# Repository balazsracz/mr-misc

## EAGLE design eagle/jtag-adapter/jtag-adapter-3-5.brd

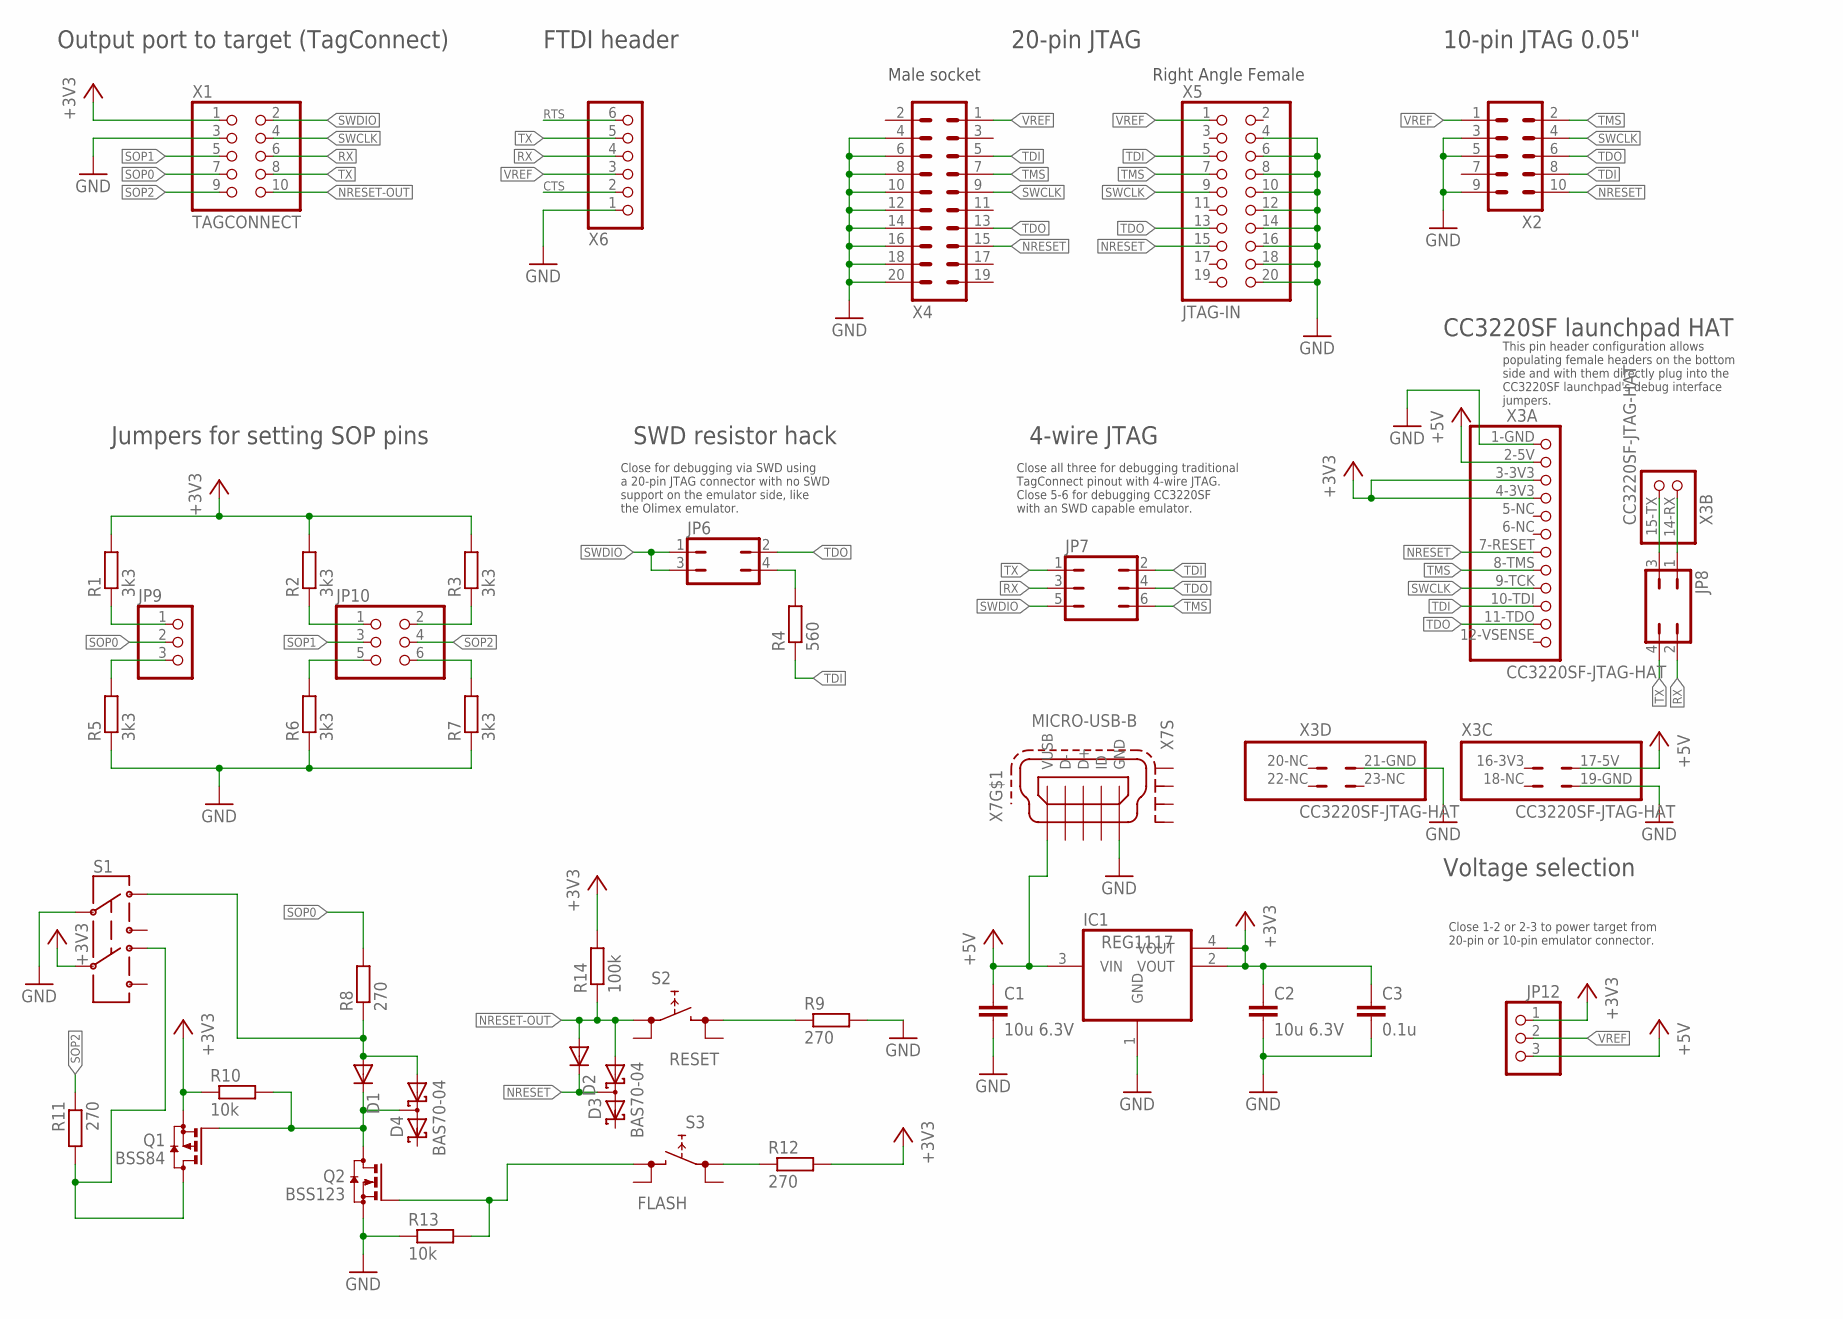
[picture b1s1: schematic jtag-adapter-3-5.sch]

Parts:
C1, C2: 10u 6.3V; C0603K
C3: 0.1u; C0603K
D1, D2: DIODE-MINIMELF; MINIMELF
D3, D4: BAS70-04; SOT23
IC1: REG1117; SOT223
JP6, JP8: JP2Q
JP7: JP3Q
JP9, JP12: PINHD-1X3; 1X03
JP10: PINHD-2X3; 2X03
Q1: BSS84; SOT23
Q2: BSS123; SOT23
R1, R2, R3, R5, R6, R7: 3k3; R0805
R4: 560; R0805
R8, R9, R11, R12: 270; R0805
R10, R13: 10k; R0805
R14: 100k; R0805
S1: SWITCH-DPDTJS202011CQN; DPDT-2.5X3.2MM
S2: RESET; TACTSW-6X6
S3: FLASH; TACTSW-6X6
X1: TAGCONNECT; CON10M
X2: MA05-2_0.05X0.05; MA05-2_0.05_X_0.05
X3: CC3220SF-JTAG-HAT; JTAG-LAUNCHPAD-3220SF
X4: MA10-2S; MA10-2-SHROUDED
X5: JTAG-IN; 2X10
X6: PINHD-1X6; 1X06
X7: MICRO-USB-B; MICRO-B-PAC

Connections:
+3V3: C2.1, C3.1, IC1.2 (VOUT), IC1.4 (VOUT), JP12.1, Q1.2 (S), R1.2, R2.2, R3.2, R10.1, R12.2, R14.2, S1.5 (2C), X1.1, X3.3-3V3 (3), X3.4-3V3 (4)
+5V: C1.1, IC1.3 (VIN), JP12.3, X3.2-5V (2), X3.17-5V (2), X7.1 (VUSB)
CTS: X6.2
FL-SOP2-PU: Q1.3 (D), R11.2, S1.4 (2A)
GND: C1.2, C2.2, C3.2, IC1.1 (GND), Q2.2 (S), R5.1, R6.1, R7.1, R9.2, R13.1, S1.2 (1C), X1.3, X2.3, X2.5, X2.9, X3.1-GND (1), X3.19-GND (4), X3.21-GND (2), X4.4, X4.6, X4.8, X4.10, X4.12, X4.14, X4.16, X4.18, X4.20, X5.4, X5.6, X5.8, X5.10, X5.12, X5.14, X5.16, X5.18, X5.20, X6.1, X7.5 (GND)
unnamed: R9.1, S2.3 (2.1)
unnamed: JP6.4, R4.2
unnamed: D1.C, D4.3 (C1A2), Q1.1 (G), Q2.3 (D), R10.2
unnamed: R12.1, S3.1 (1.1)
unnamed: Q2.1 (G), R13.2, S3.3 (2.1)
unnamed: JP8.1, X3.14-RX (1)
unnamed: JP8.3, X3.15-TX (2)
unnamed: D1.A, D4.1 (A1), R8.1, S1.1 (1A)
NRESET: D2.C, D3.3 (C1A2), X2.10, X3.7-RESET (7), X4.15, X5.15
NRESET-OUT: D2.A, D3.1 (A1), R14.1, S2.1 (1.1), X1.10
RTS: X6.6
RX: JP7.3, JP8.2, X1.6, X6.4
SOP0: JP9.2, R8.2, X1.7
SOP0H: JP9.1, R1.1
SOP0L: JP9.3, R5.2
SOP1: JP10.3, X1.5
SOP1H: JP10.1, R2.1
SOP1L: JP10.5, R6.2
SOP2: JP10.4, R11.1, X1.9
SOP2H: JP10.2, R3.1
SOP2L: JP10.6, R7.2
SWCLK: X1.4, X2.4, X3.9-TCK (9), X4.9, X5.9
SWDIO: JP6.1, JP6.3, JP7.5, X1.2
TDI: JP7.2, R4.1, X2.8, X3.10-TDI (10), X4.5, X5.5
TDO: JP6.2, JP7.4, X2.6, X3.11-TDO (11), X4.13, X5.13
TMS: JP7.6, X2.2, X3.8-TMS (8), X4.7, X5.7
TX: JP7.1, JP8.4, X1.8, X6.5
VREF: JP12.2, X2.1, X4.1, X5.1, X6.3

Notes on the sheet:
Output port to target (TagConnect)
Jumpers for setting SOP pins
4-wire JTAG
SWD resistor hack
FTDI header
20-pin JTAG
10-pin JTAG 0.05"
Right Angle Female
Male socket
Voltage selection
CC3220SF launchpad HAT
This pin header configuration allows populating female headers on the bottom side and with them directly plug into the CC3220SF launchpad's debug interface jumpers.
Close for debugging via SWD using a 20-pin JTAG connector with no SWD support on the emulator side, like the Olimex emulator.
Close all three for debugging traditional TagConnect pinout with 4-wire JTAG. Close 5-6 for debugging CC3220SF with an SWD capable emulator.
Close 1-2 or 2-3 to power target from 20-pin or 10-pin emulator connector.

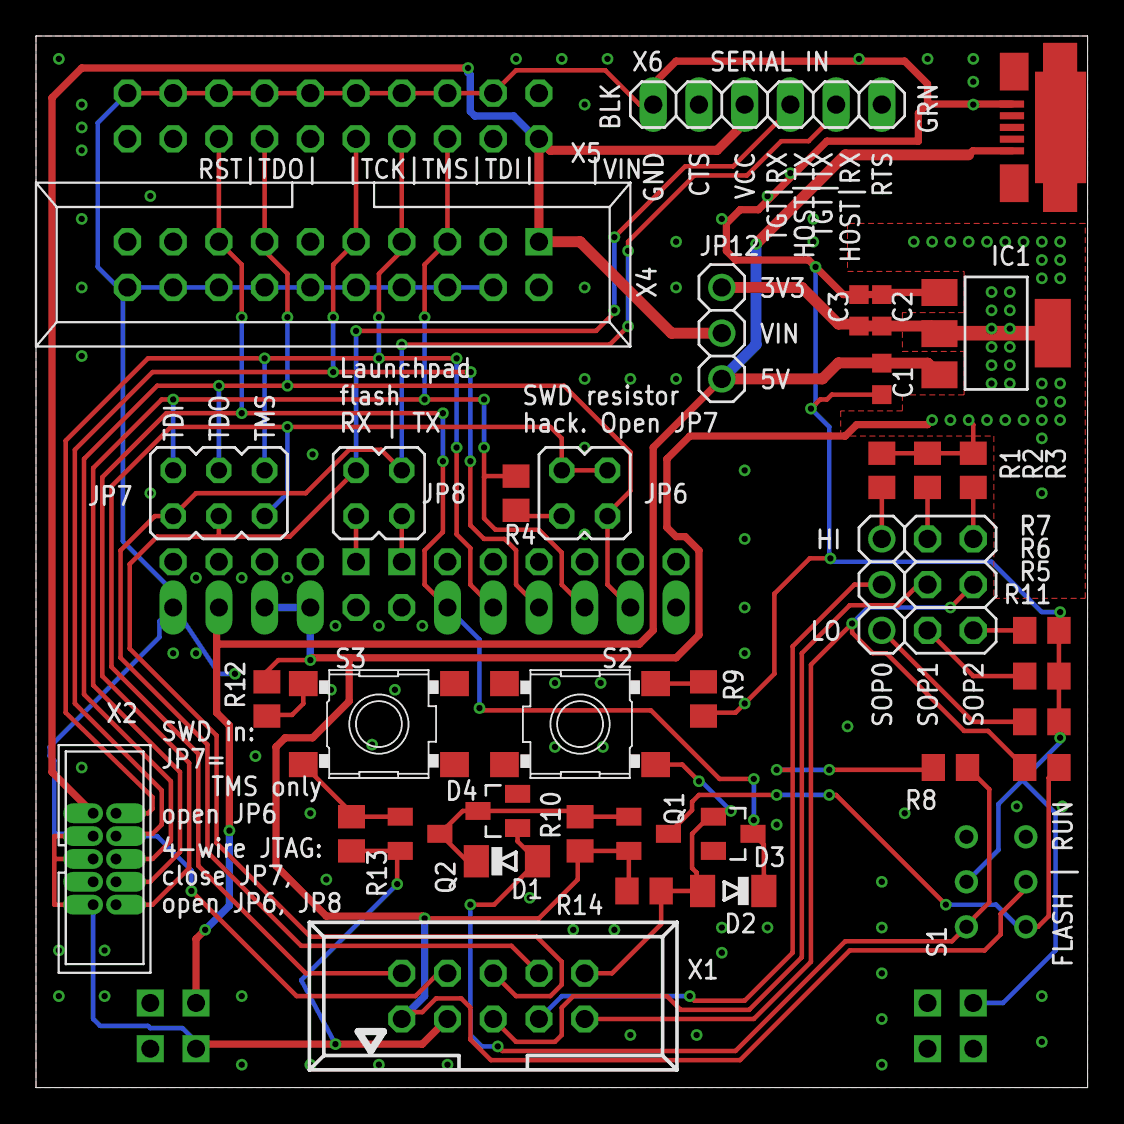
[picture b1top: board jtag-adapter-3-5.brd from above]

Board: 2 copper layers, 58.4 x 58.4 mm, 40 parts (1 on the bottom side), 31 nets.

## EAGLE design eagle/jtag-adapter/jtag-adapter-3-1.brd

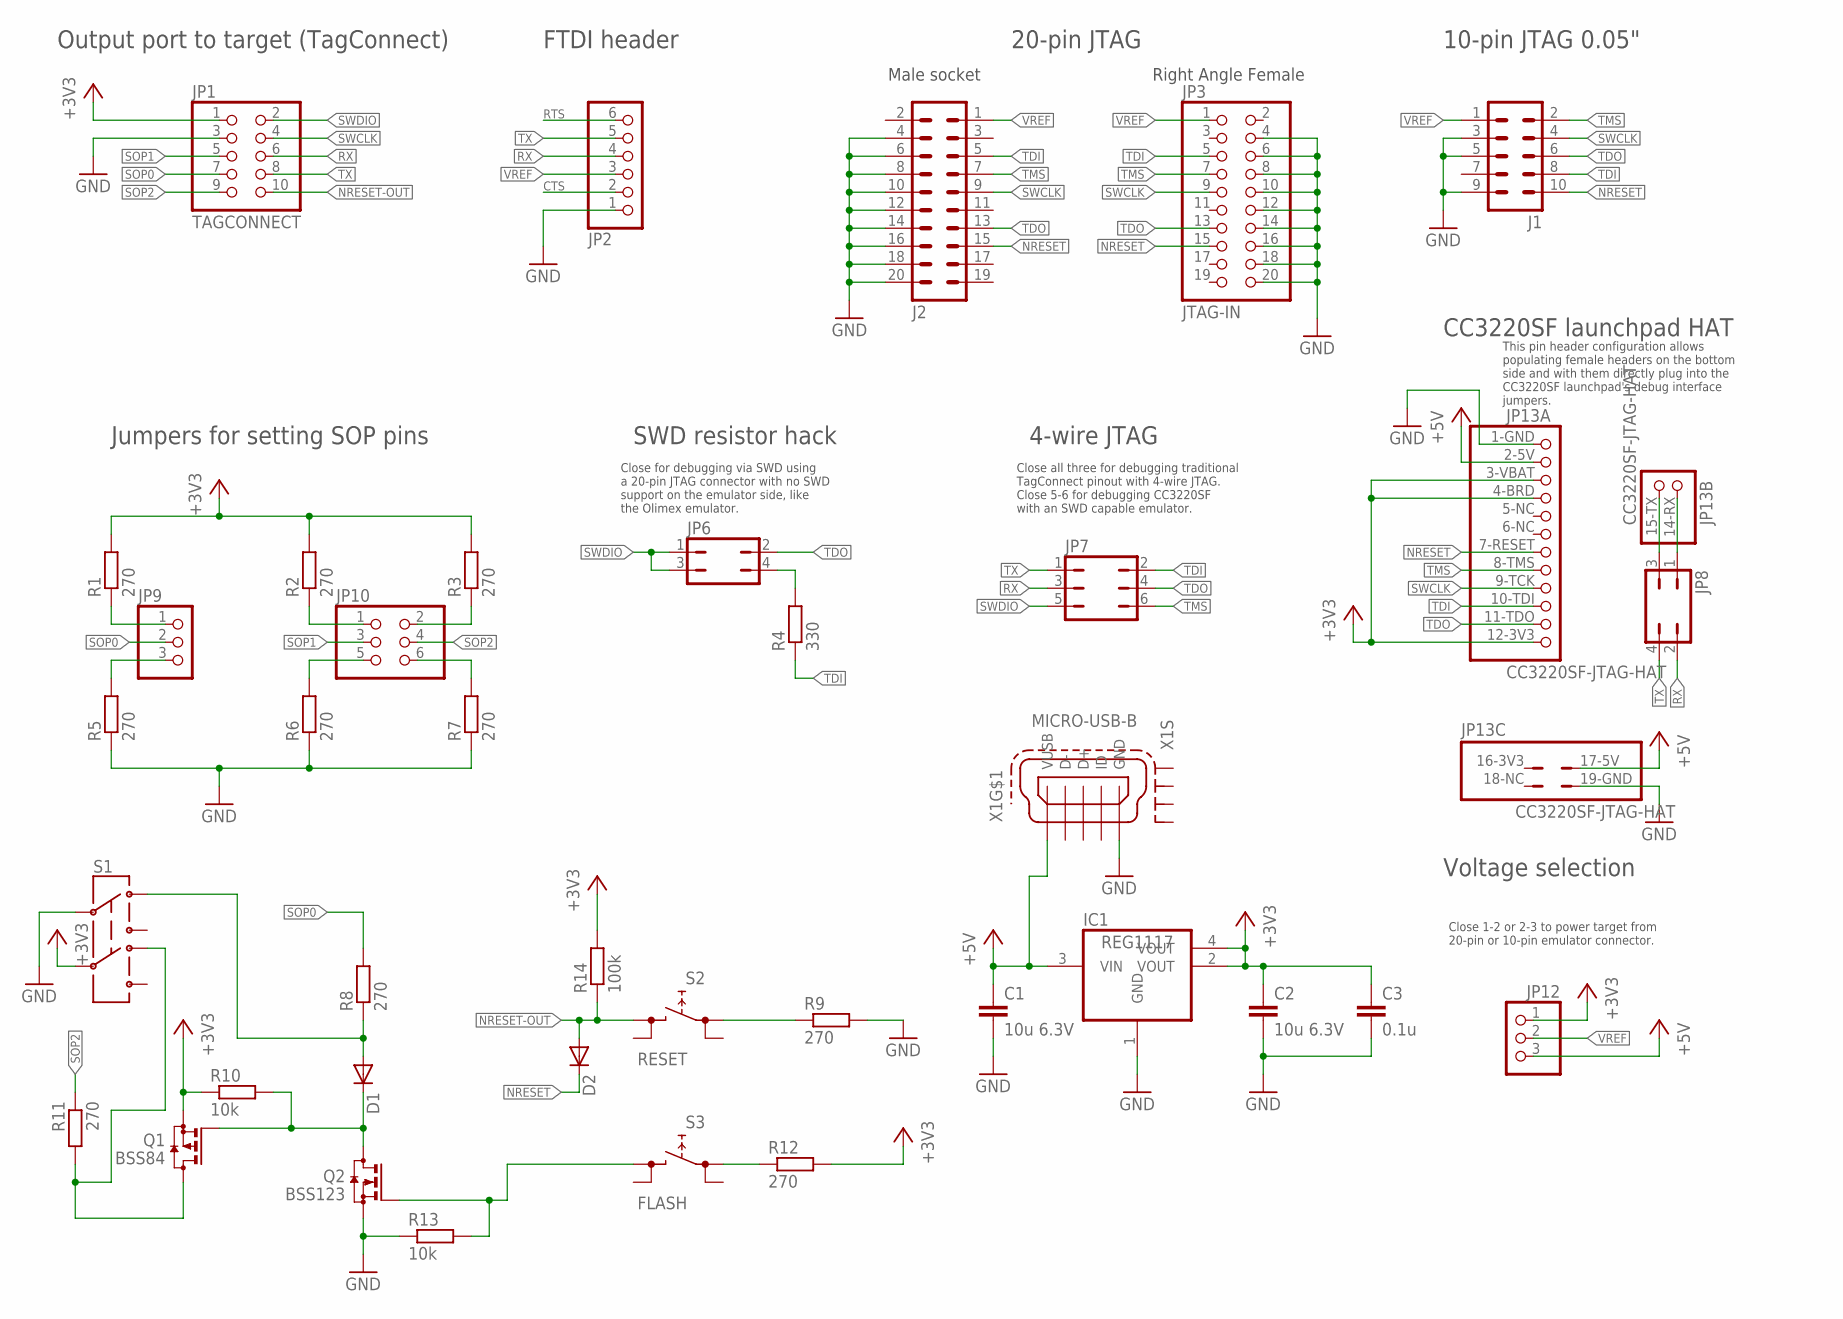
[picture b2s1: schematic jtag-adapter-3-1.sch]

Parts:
C1, C2: 10u 6.3V; C0603K
C3: 0.1u; C0603K
D1, D2: DIODE-MINIMELF; MINIMELF
IC1: REG1117; SOT223
J1: MA05-2_0.05X0.05; MA05-2_0.05_X_0.05
J2: MA10-2S; MA10-2-SHROUDED
JP1: TAGCONNECT; CON10M
JP2: PINHD-1X6; 1X06
JP3: JTAG-IN; 2X10
JP6, JP8: JP2Q
JP7: JP3Q
JP9, JP12: PINHD-1X3; 1X03
JP10: PINHD-2X3; 2X03
JP13: CC3220SF-JTAG-HAT; JTAG-LAUNCHPAD-3220SF
Q1: BSS84; SOT23
Q2: BSS123; SOT23
R1, R2, R3, R5, R6, R7, R8, R9, R11, R12: 270; R0805
R4: 330; R0805
R10, R13: 10k; R0805
R14: 100k; R0805
S1: SWITCH-DPDTJS202011CQN; DPDT-2.5X3.2MM
S2: RESET; TACTSW-6X6
S3: FLASH; TACTSW-6X6
X1: MICRO-USB-B; MICRO-B-PAC

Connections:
+3V3: C2.1, C3.1, IC1.2 (VOUT), IC1.4 (VOUT), JP1.1, JP12.1, JP13.3-VBAT (3), JP13.4-BRD (4), JP13.12-3V3 (12), Q1.2 (S), R1.2, R2.2, R3.2, R10.1, R12.2, R14.2, S1.5 (2C)
+5V: C1.1, IC1.3 (VIN), JP12.3, JP13.2-5V (2), JP13.17-5V (2), X1.1 (VUSB)
CTS: JP2.2
GND: C1.2, C2.2, C3.2, IC1.1 (GND), J1.3, J1.5, J1.9, J2.4, J2.6, J2.8, J2.10, J2.12, J2.14, J2.16, J2.18, J2.20, JP1.3, JP2.1, JP3.4, JP3.6, JP3.8, JP3.10, JP3.12, JP3.14, JP3.16, JP3.18, JP3.20, JP13.1-GND (1), JP13.19-GND (4), Q2.2 (S), R5.1, R6.1, R7.1, R9.2, R13.1, S1.2 (1C), X1.5 (GND)
unnamed: R9.1, S2.1 (1.1)
unnamed: JP6.4, R4.2
unnamed: D1.C, Q1.1 (G), Q2.3 (D), R10.2
unnamed: R12.1, S3.1 (1.1)
unnamed: Q2.1 (G), R13.2, S3.3 (2.1)
unnamed: Q1.3 (D), R11.2, S1.4 (2A)
unnamed: JP8.1, JP13.14-RX (1)
unnamed: JP8.3, JP13.15-TX (2)
unnamed: D1.A, R8.1, S1.1 (1A)
NRESET: D2.C, J1.10, J2.15, JP3.15, JP13.7-RESET (7)
NRESET-OUT: D2.A, JP1.10, R14.1, S2.3 (2.1)
RTS: JP2.6
RX: JP1.6, JP2.4, JP7.3, JP8.2
SOP0: JP1.7, JP9.2, R8.2
SOP0H: JP9.1, R1.1
SOP0L: JP9.3, R5.2
SOP1: JP1.5, JP10.3
SOP1H: JP10.1, R2.1
SOP1L: JP10.5, R6.2
SOP2: JP1.9, JP10.4, R11.1
SOP2H: JP10.2, R3.1
SOP2L: JP10.6, R7.2
SWCLK: J1.4, J2.9, JP1.4, JP3.9, JP13.9-TCK (9)
SWDIO: JP1.2, JP6.1, JP6.3, JP7.5
TDI: J1.8, J2.5, JP3.5, JP7.2, JP13.10-TDI (10), R4.1
TDO: J1.6, J2.13, JP3.13, JP6.2, JP7.4, JP13.11-TDO (11)
TMS: J1.2, J2.7, JP3.7, JP7.6, JP13.8-TMS (8)
TX: JP1.8, JP2.5, JP7.1, JP8.4
VREF: J1.1, J2.1, JP2.3, JP3.1, JP12.2

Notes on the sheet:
Output port to target (TagConnect)
Jumpers for setting SOP pins
4-wire JTAG
SWD resistor hack
FTDI header
20-pin JTAG
10-pin JTAG 0.05"
Right Angle Female
Male socket
Voltage selection
CC3220SF launchpad HAT
This pin header configuration allows populating female headers on the bottom side and with them directly plug into the CC3220SF launchpad's debug interface jumpers.
Close for debugging via SWD using a 20-pin JTAG connector with no SWD support on the emulator side, like the Olimex emulator.
Close all three for debugging traditional TagConnect pinout with 4-wire JTAG. Close 5-6 for debugging CC3220SF with an SWD capable emulator.
Close 1-2 or 2-3 to power target from 20-pin or 10-pin emulator connector.

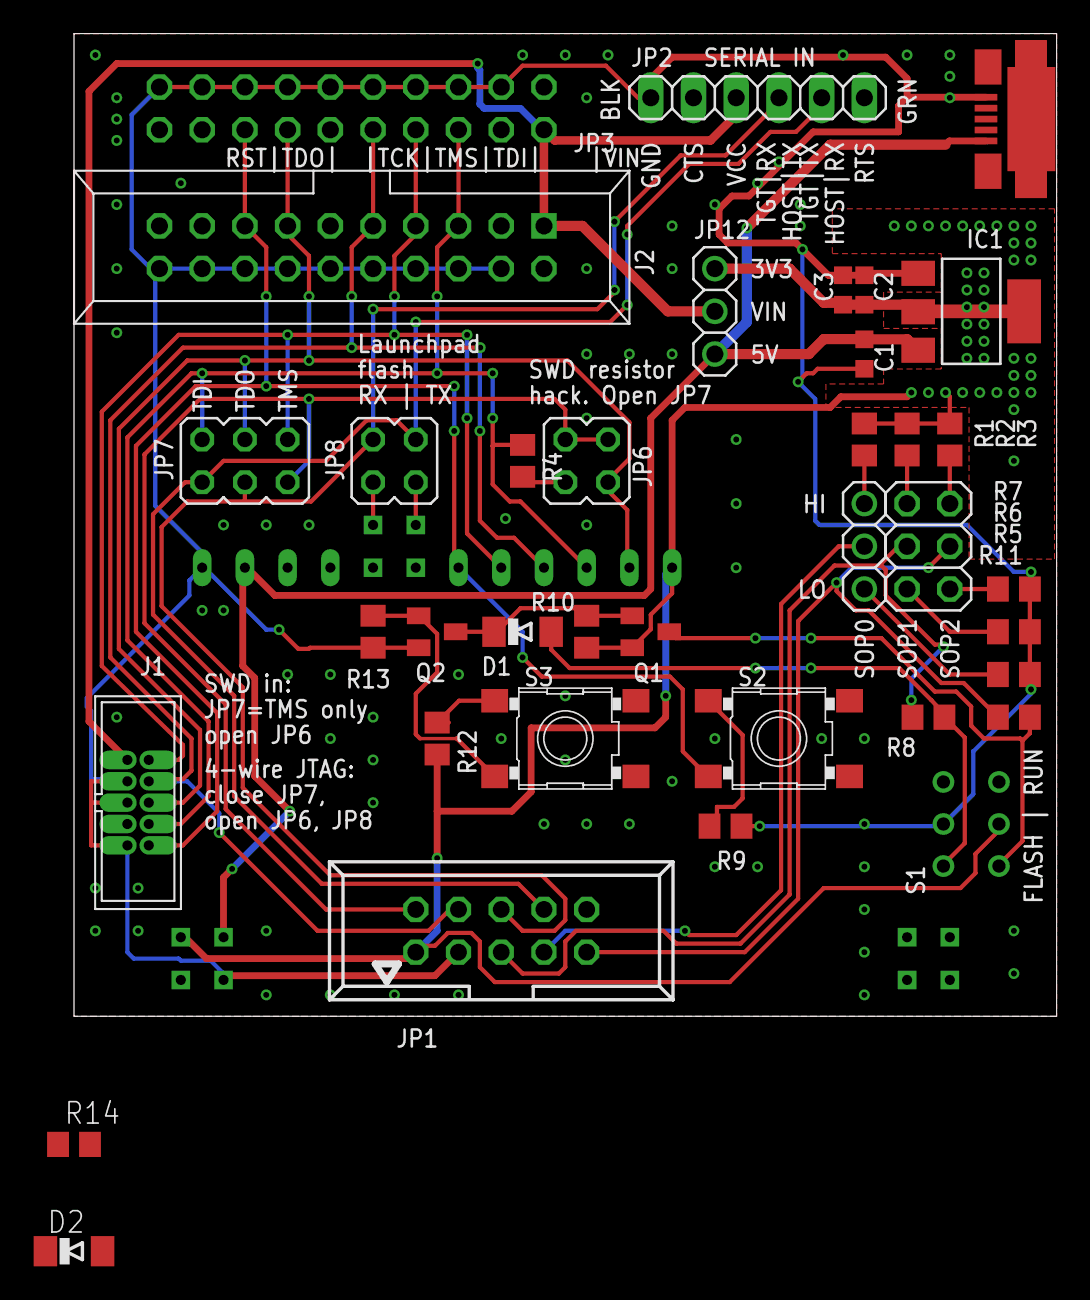
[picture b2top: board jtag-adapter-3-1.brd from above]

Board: 2 copper layers, 58.4 x 58.4 mm, 38 parts (1 on the bottom side), 31 nets.

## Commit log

2011-10-30 add initial list of stuff
2011-10-30 Baseline boxing command
2011-10-30 Add resistor definition command.
2011-10-30 check in CSV list
2011-11-05 finished labels tex code
2013-08-10 Workshop list generation code updates.
2013-08-10 Original source and binaries by D Nadler.
2013-08-10 Adds XC32 headers that are needed for the peripherial definitions.
2013-08-10 Changes needed to make the cpp demo compile.
2013-08-10 Removes generated files.
2013-08-10 Allows make dep to run without an exisitng depend file.
2013-08-12 Fixes compilation problems.
2013-08-12 Adpts nadler's code to PIC32MX795 on my board.
2013-08-12 Adds bootloader code with changes needed to make it compile.
2013-08-12 Adds missing file for the 795.
2013-08-12 Switches bootloader to 80MHz. Updates USB bootloader to not require interrupt flag table, which is huge. Renamed to bootloader.{elf,hex} Removes the CS3 startup code which is huge. Supplies custom st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
2013-08-12 Moves the bootloader into the bootloader area. Updates the app start pointers.
2013-08-12 Working bootloader.
2014-06-06 Updates the fuses to match the duinomite mega better. Enables block switching.
2014-06-06 Fixes compilation errors.
2014-06-06 changes the include guard to avoid clashes with openmrn.
2014-06-06 updates bootloader fuses.
2015-03-16 Adds base versions of the mixxx controller scripts.
2015-03-16 Removes the headphone volume control. Adds script bindings to the fwd and back buttons.
2015-03-16 starts adding onfwd onback javascript functions.
2015-03-16 Adds handling for onFwd.
2015-03-16 removes key off bindings from the onfwd onback commands.
2015-03-16 Fixes bug in onFwd that caused it to trigger on key up as well.
2015-03-16 Adds onBack implementation.
2015-03-16 Fixes broken script-binding.
2015-03-16 Adds a couple of buttons as soft buttons.
2015-03-16 Implements beats translation on soft button 4.
2015-04-19 moves an onsoftbutton defn.
2015-04-19 Adds the ability to catch wheel turn (not jog) operations in javascript.
2015-05-14 adds scratching support when the deck is not playing.
2015-10-25 'We use math' tex logo.
2015-10-25 adds gitignore for parts.
2015-10-25 adds gitignore.
2015-10-25 trainlib historical commit 2014-10-31
2015-10-25 trainlib historical commit 2014-10-31-2
2015-10-25 trainlib historical commit 2014-10-31-3
2015-10-25 trainlib historical commit 2014-10-31-4
2015-10-25 trainlib historical commit 2014-11-01-1
2015-10-25 trainlib historical commit 2014-11-01-2
2015-10-25 trainlib historical commit 2014-11-01-3
2015-10-25 trainlib historical commit 2015-07-25-1
2015-10-25 trainlib historical commit 2015-07-25-3
2015-10-25 trainlib historical commit 2015-07-27-1
2015-10-25 trainlib historical commit 2015-07-27-2
2015-10-25 trainlib historical commit 2015-08-31-1
2015-10-25 trainlib historical commit 2015-08-31-2
2015-10-25 trainlib historical commit 2015-08-31-3
2015-10-25 trainlib historical commit 2015-08-31-4
2015-10-25 trainlib current
2015-10-26 adds/updates rj45 jacks. adds a 0R bridge.
2015-11-27 smd reflow oven testing pattern
2015-11-27 Adds basic makefile and blink binary
2015-11-27 Adds qr code files.
2015-11-27 checks in bootloader source
2015-11-29 Adds eagle library file used by the project.
2015-12-01 adds a test of the led hardware during the bootup of the bootloader.
2015-12-01 cleanup library
2015-12-02 original bootloader offset
2015-12-02 updates codeoffset.
2015-12-02 removes outpout file
2015-12-02 ignores hex files
2015-12-02 Adds usb driver source to firmware library.
2015-12-02 adds usb options to makefile
2015-12-02 rendered schematics
2015-12-02 older version
2015-12-02 adds gitignore
2015-12-02 updates yellow on rgb
2015-12-02 cleanup blink code
2015-12-02 Adds all the steps for the firmware training.
2015-12-03 Adds binaries for flashing usb-hid bootloaders.
2015-12-03 adds mac specific makefile
2015-12-03 create bin dir
2015-12-03 actually use the flash variable
2015-12-08 Adds production firmware.
2016-05-15 Adds a test application to debug the USB-CDC device driver.
2016-05-15 Adds new device DMG6601LVT.
2016-05-15 Adds esp12-huzzah breakout board.
2016-05-15 Adds pololu voltage regulator.
2016-05-15 Finishes deadrail schematics (en gross).
2016-05-17 Adds esp12-huzzah board definition.
2016-05-17 autorouter definitions for etching.
2016-05-17 Adds all intermediate and the final schematic and board layout for the huzzah baseboard for esp-12 train decoder.
2016-06-04 Adds a bunch of parts to the lib that are used in the deadrail controller.
2016-06-04 Checks in the adafruit eagle library downloaded from their webpage.
2016-06-04 Adds first versions of the schematics for the native deadrail decoder implementation.
2016-06-05 Adds through-hole version of esp-12. Adds rectifier bridge in sot format. Adds analog mux. Adds pinheaders for hand soldering.
2016-06-05 Fixes unloadable schematics
2016-06-05 Adds all intermediate and the final rendering of the design.
2016-06-06 Adds the esp-12 in the original form from the adafruit library and makes the rounding outline smaller.
2016-06-06 Adds variants with polygon and a bunch of ground vias.
2016-06-06 Adds gerber output.
2016-06-23 submitted file.
2016-07-26 Check in compiled version of the bootloader (with full optimization so it fits in 4K).
2016-07-26 Adds dependency list.
2016-07-27 Adds a firmware that can be used to test the solder job.
2016-07-28 Stop sending zeros to the hostfrom the usb-serial device. It makes various host program confused.
2016-07-28 Change the USB-reported product name so that we can recognize these devices from software.
2016-07-28 Adds trim dependency.
2016-07-28 Adds data logger application that writes to google sheets.
2016-07-28 Actually call init().
2016-09-07 update DRU
2016-09-07 Check in ledmatrix rules.
2016-09-09 continue work on the ledmatrix schematic and board.
2016-09-09 Adds outlines.
2016-09-09 adds brokenusb test
2016-09-09 layout components.
2016-09-09 more routing -- latch, clock proposal 1
2016-09-09 all routed
2016-09-09 adds ground fill.
2016-09-09 regenrates fill. Adds rendered board.
2017-05-06 Adds drawing of the laser-cutted bridge.
2017-05-06 Adds new versions of the bridge design.
2017-05-07 New design with small fixes of the bridge
2018-04-01 Checks in missing files.
2018-04-01 Adds nucleo 64 library element.
2018-04-01 Start of the io board based on the nucleo base.
2018-04-05 Adds AP1509 and a through hole inductor.
2018-04-05 Adds version of the nucleo board with inputs, the switching PS and part of the tortoise driver.
2018-04-09 Ignores backup files by eagle.
2018-04-09 Adds seed DRU file
2018-04-09 Adds round solder jumpers; solder jumpers that are default-closed Updates DIL-8 package to have standard footprint Adds package outline to 0.1" terminal block Adds DIL18 footprint with small solder t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
2018-04-09 More work on the nucleo io board.
2018-04-14 more versions of the io board.
2018-04-15 Adds better (polygon based) round solder bridge. Moves CAN transceiver to create a small-hole DIL8 package version.
2018-04-15 Finishes routing the io board. Adds four more servo outputs.
2018-04-19 Latest versions.
2018-04-22 updates some components.
2018-04-22 Adds more iterations of the io board.
2018-05-06 Moves layer designations for the power notice component.
2018-05-06 Adds a package for denoting revision.
2018-05-06 Removes the ground polygon inside the cutaway wire of the SJ-C.
2018-05-06 Rev A final version.
2018-05-06 Moves a couple of parts to the custom library to allow renaming prefix to U instead of IC.
2018-05-06 Progress towards rev B.
2018-05-06 Adds missing prefixes.
2018-05-08 Modifies the DC jack part to not have overlapping mills and drill.
2018-05-08 New revisions to fix comments from the review process.
2018-05-12 More versions of the board design.
2018-05-12 DCjack: removes overlapping wires on the via layer that cause conflict.
2018-05-21 Adds DPDT switch adds micro-USB receptacle adds larger pinheaders adds a CC3220SF launchpad HAT footprint.
2018-05-21 Adds programming adapter board.
2018-05-21 adds individual gerber files of the jtag adapter.
2018-05-21 Adds RJ45 adaptor board.
2018-05-23 Adds deduplicator python code.
2018-05-23 Adds copyright notice
2018-05-26 Adds first covering algorithm.
2018-05-26 Adds code to apply rules specifically to filter files with lots of duplicates.
2018-06-11 Fixes launchpad jtag-HAT footprint. Fixes bounding box on siklscreen for the 0.05" jtag header.
2018-06-11 Fixes prototype problems.
2018-07-07 Imports loconet library from arduino library manager.
2018-07-07 Adds empty shell for openmrn library.
2018-07-08 moves library to src directory for 1.5. format.
2018-07-08 switches library to .a linkage.
2018-07-08 Adds symlinks to the openmrn implementation code.
2018-07-08 Adds support for Serial ports via gridconnect hub.
2018-07-24 Adds code for CAN bridge.
2018-07-24 Adds more symlinks for arduino codebase.
2018-07-24 Adds example sketch with openmrn.
2018-07-24 Adds another test copy of the arduino library.
2018-09-09 Fix inlining problem with new GCC compilation.
2018-09-10 recompiles bootloader.
2019-01-13 Updates resistor values.
2019-01-13 Updates frame grid.
